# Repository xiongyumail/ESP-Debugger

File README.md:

# ESP-Debugger

## How to use
```bash
git clone --recursive https://github.com/xiongyumail/esp-debugger
```
## Show

## Schematic

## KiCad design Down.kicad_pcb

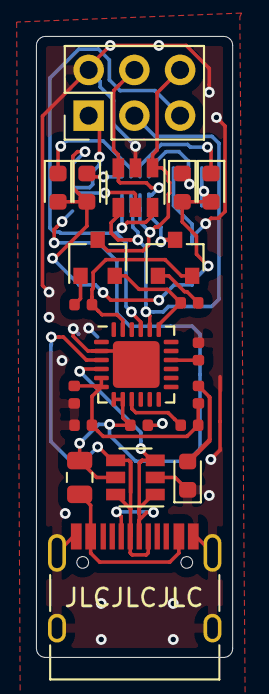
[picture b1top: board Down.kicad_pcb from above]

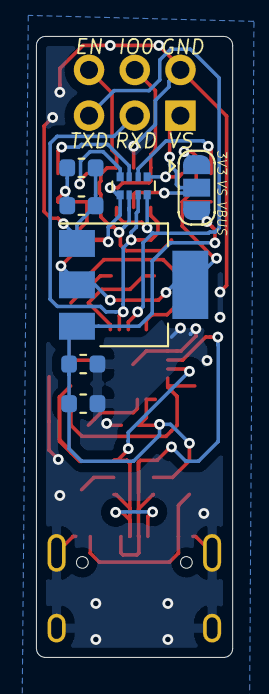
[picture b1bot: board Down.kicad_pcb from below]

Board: 2 copper layers, 10.9 x 34.5 mm, 28 parts (7 on the bottom side), 23 nets.

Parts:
C1, C3: 10uF; C_0603_1608Metric
C2, C4: 1uF; C_0603_1608Metric
C5: 4.7uF; C_0402_1005Metric
C6, C8: 1uF; C_0402_1005Metric
C7: 0.1uF; C_0402_1005Metric
D1, D2, D3, D4, D5: LED; LED_0603_1608Metric
F1: PPTC; Fuse_0805_2012Metric
J1: Conn_02x03_Odd_Even; PinHeader_2x03_P2.54mm_Vertical
J2: HRO_TYPE-C-31-M-12
JP1: SolderJumper_3_Open; SolderJumper-3_P1.3mm_Open_RoundedPad1.0x1.5mm
Q1, Q2: S9014; SOT-23
R1: 10K; R_0402_1005Metric
R2, R3, R4: 1K; R_0402_1005Metric
RN1: 1K; R_Array_Convex_4x0402
U2, U3: SRV05-4; SOT-23-6
U4: AMS1117-LDO; SOT-223
U5: CP2104; QFN-24-1EP_4x4mm_P0.5mm_EP2.6x2.6mm

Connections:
+3V3: C3.1, C4.1, D1.2, D2.2, D3.2, D4.2, JP1.1, U4.2, U4.4
/CP2104/DTR: Q2.2, R2.1, U5.23
/CP2104/RTS: Q1.2, R3.1, U5.19
/CP2104/VDD3V45: C7.2, C8.2, R1.2, R4.1, U5.5, U5.6
/D+: J2.A6, J2.B6, U2.4, U2.6, U5.3
/D-: J2.A7, J2.B7, U2.1, U2.3, U5.4
/EN: J1.6, Q1.3, RN1.2, U3.1
/IO0: J1.4, Q2.3, RN1.1, U3.3
/RXD: J1.3, RN1.3, U3.4, U5.20
/TXD: J1.5, RN1.4, U3.6, U5.21
GND: C1.2, C2.2, C3.2, C4.2, C5.2, C6.1, C7.1, C8.1, D5.1, J1.2, J2.A1, J2.A12, J2.B1, J2.B12, J2.S1, U2.2, U3.2, U4.1, U5.2, U5.25
unnamed: C5.1, U5.16
unnamed: D1.1, RN1.8
unnamed: D2.1, RN1.7
unnamed: D3.1, RN1.6
unnamed: D4.1, RN1.5
unnamed: D5.2, R4.2
unnamed: F1.2, J2.A4, J2.A9, J2.B4, J2.B9
unnamed: Q1.1, R2.2
unnamed: Q2.1, R3.2
unnamed: R1.1, U5.9
VBUS: C1.1, C2.1, C6.2, F1.1, JP1.3, U2.5, U4.3, U5.7, U5.8
VS: J1.1, JP1.2, U3.5

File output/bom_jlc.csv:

Comment,Description,Designator,Footprint,LibRef,Pins,Quantity
Conn_02x03_Odd_Even,J1,J1,Connector_PinHeader_2.54mm:PinHeader_2x03_P2.54mm_Vertical,,2,1
LED,D1,D1,LED_SMD:LED_0603_1608Metric,C2286,2,1
LED,D2,D2,LED_SMD:LED_0603_1608Metric,C72038,2,1
LED,D3,D3,LED_SMD:LED_0603_1608Metric,C72043,2,1
LED,D4,D4,LED_SMD:LED_0603_1608Metric,C72041,2,1
1K,RN1,RN1,Resistor_SMD:R_Array_Convex_4x0402,C25726,2,1
SRV05-4-P-T7,U2,U2,Package_TO_SOT_SMD:SOT-23-6,C85364,6,1
SRV05-4-P-T7,U3,U3,Package_TO_SOT_SMD:SOT-23-6,C85364,6,1
PPTC,F1,F1,Fuse:Fuse_0805_2012Metric,C17477,2,1
SolderJumper_3_Open,JP1,JP1,Jumper:SolderJumper-3_P1.3mm_Open_RoundedPad1.0x1.5mm,,2,1
HRO_TYPE-C-31-M-12,J2,J2,USB:HRO_TYPE-C-31-M-12,,2,1
AMS1117-3.3,U4,U4,Package_TO_SOT_SMD:SOT-223,C6186,2,1
10uF,C1,C1,0603,C19702,2,1
1uF,C2,C2,0603,C15849,2,1
10uF,C3,C3,0603,C19702,2,1
1uF,C4,C4,0603,C15849,2,1
CP2104,U5,U5,Package_DFN_QFN:QFN-24-1EP_4x4mm_P0.5mm_EP2.6x2.6mm,,2,1
S8050,Q1,Q1,Package_TO_SOT_SMD:SOT-23,C2146,3,1
S8050,Q2,Q2,Package_TO_SOT_SMD:SOT-23,C2146,3,1
4.7uF,C5,C5,Capacitor_SMD:C_0402_1005Metric,C23733,2,1
10K,R1,R1,Resistor_SMD:R_0402_1005Metric,C25744,2,1
1uF,C8,C8,Capacitor_SMD:C_0402_1005Metric,C52923,2,1
0.1uF,C7,C7,Capacitor_SMD:C_0402_1005Metric,C1525,2,1
1uF,C6,C6,Capacitor_SMD:C_0402_1005Metric,C52923,2,1
1K,R3,R3,Resistor_SMD:R_0402_1005Metric,C11702,2,1
1K,R2,R2,Resistor_SMD:R_0402_1005Metric,C11702,2,1
LED,D5,D5,LED_SMD:LED_0603_1608Metric,C2290,2,1
1K,R4,R4,Resistor_SMD:R_0402_1005Metric,C11702,2,1

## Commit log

2019-08-22 clean project
2020-08-10 add convert.py
2020-08-12 add Down_cp
